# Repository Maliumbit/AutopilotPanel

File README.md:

# AutopilotPanel
Autopilot Controller

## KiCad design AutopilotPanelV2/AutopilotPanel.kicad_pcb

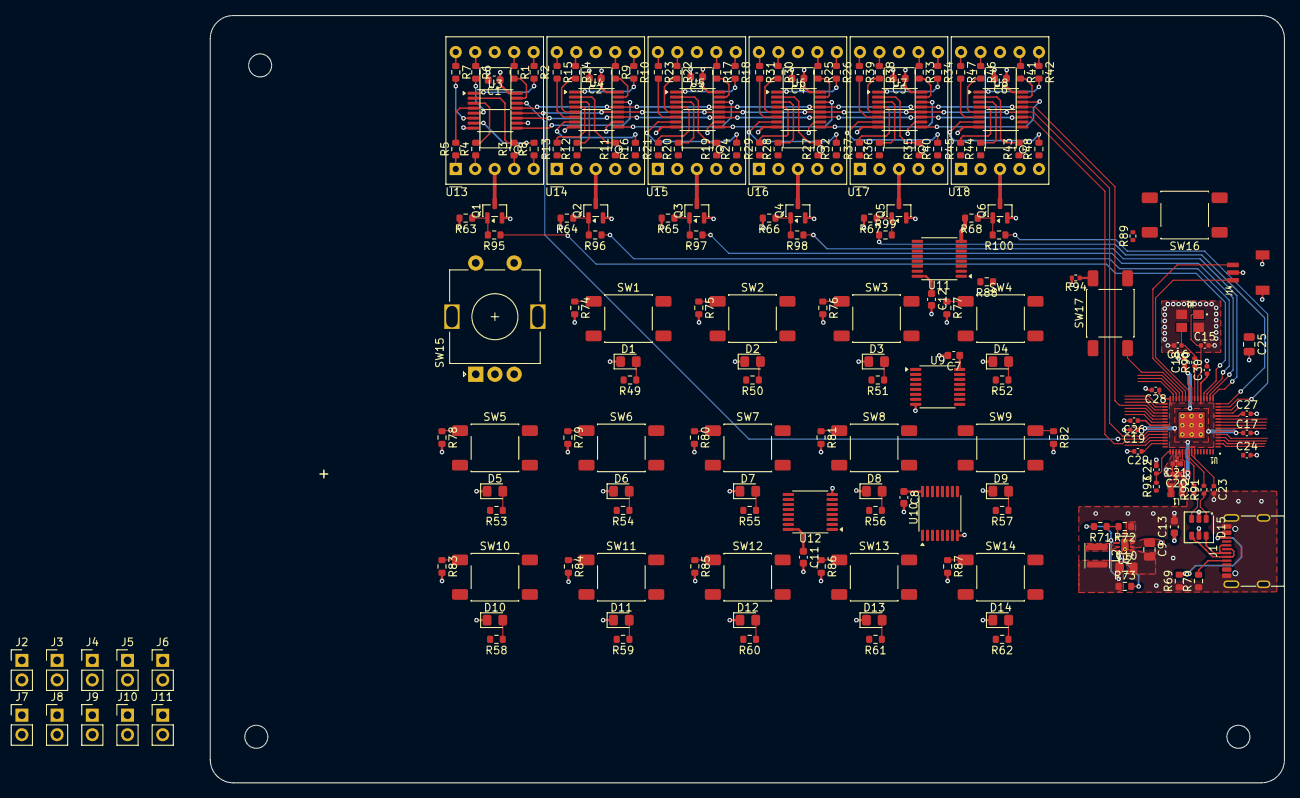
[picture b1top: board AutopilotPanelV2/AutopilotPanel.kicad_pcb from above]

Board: 6 copper layers, 140.0 x 100.0 mm, 200 parts (0 on the bottom side), 203 nets.

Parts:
C1, C2, C3, C4, C5, C6, C7, C8, C11, C12, C13: 100nF; C_0603_1608Metric
C9: 10uF; C_0805_2012Metric
C10: 22uF; C_0805_2012Metric
C15, C16: 15p; C_0402_1005Metric
C17, C18, C19, C23, C24, C26, C27, C28, C29, C30: 100n; C_0402_1005Metric
C20, C21, C22: 4.7u; C_0402_1005Metric
C25: 10u; C_0805_2012Metric
D1, D2, D3, D4, D5, D6, D7, D8, D9, D10, D11, D12, D13, D14: LED_Green_0805; LED_0805_2012Metric_Pad1.15x1.40mm_HandSolder
D15: USBLC6-2SC6; SOT-23-6
J1: USB_C_Receptacle_USB2.0_16P; USB_C_Receptacle_G-Switch_GT-USB-7010ASV
J2, J3, J4, J5, J6, J7, J8, J9, J10, J11: PINHD_1x2_Male; PinHeader_1x02_P2.54mm_Vertical
J14: SM03B-SRSS-TB(LF)(SN); jst_sm03b-srss-tb-lf--sn-
L1: 3.3u; abracon_aota-b201610s3r3-101-t
L2: 2.2uH; L_Changjiang_FNR3015S
Q1, Q2, Q3, Q4, Q5, Q6: NFET-SOT23; SOT-23
R1, R2, R3, R4, R5, R6, R7, R8, R9, R10, R11, R12, R13, R14, R15, R16, R17, R18, R19, R20, R21, R22, R23, R24, R25, R26, R27, R28, R29, R30, R31, R32, R33, R34, R35, R36, R37, R38, R39, R40, R41, R42, R43, R44, R45, R46, R47, R48, R49, R50, R51, R52, R53, R54, R55, R56, R57, R58, R59, R60, R61, R62: 330; R_0603_1608Metric
R63, R64, R65, R66, R67, R68, R74, R75, R76, R77, R78, R79, R80, R81, R82, R83, R84, R85, R86, R87, R88: 10k; R_0603_1608Metric
R69, R70: 5.1k; R_0603_1608Metric
R71: 562k; R_0603_1608Metric
R72: 180k; R_0603_1608Metric
R73: 100k; R_0603_1608Metric
R89, R90, R94: 1k; R_0402_1005Metric
R91, R92: 27; R_0402_1005Metric
R93: 33; R_0402_1005Metric
R95, R96, R97, R98, R99, R100: 100; R_0603_1608Metric
SW1, SW2, SW3, SW4, SW5, SW6, SW7, SW8, SW9, SW10, SW11, SW12, SW13, SW14, SW16, SW17: SW_SPST_Tactile_6x6; SW_Push_1P1T_NO_E-Switch_TL3301NxxxxxG
SW15: RotaryEncoder_Switch_EC11E; RotaryEncoder_Alps_EC11E-Switch_Vertical_H20mm
U1: RP2354A; rpi_rp2350a_vias
U2: TPS62160DSG; Texas_DSG0008A_WSON-8-1EP_2x2mm_P0.5mm_EP0.9x1.6mm_ThermalV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
U3, U4, U5, U6, U7, U8, U9, U10: 74HC595; TSSOP-16_4.4x5mm_P0.65mm
U11, U12: 74HC165; TSSOP-16_4.4x5mm_P0.65mm
U13, U14, U15, U16, U17, U18: 7SegmentFJ5161AH; D1X8K
X1: 12MHz; generic_xtalcc320x250x80-4

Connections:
+1.1V: C17.1, C18.1, C19.1, C20.1, L1.1, U1.6 (DVDD), U1.23 (DVDD), U1.39 (DVDD), U1.50 (VREG_FB)
+3.3V: C1.1, C2.1, C3.1, C4.1, C5.1, C6.1, C7.1, C8.1, C10.1, C11.1, C12.1, C21.1, C23.1, C24.1, C25.1, C26.1, C27.1, C28.1, C29.1, C30.1, J3.1, L2.2, R71.2, R73.1, R88.1, R93.1, SW1.2 (B), SW2.2 (B), SW3.2 (B), SW4.2 (B), SW5.2 (B), SW6.2 (B), SW7.2 (B), SW8.2 (B), SW9.2 (B), SW10.2 (B), SW11.2 (B), SW12.2 (B), SW13.2 (B), SW14.2 (B), U1.1 (IOVDD), U1.11 (IOVDD), U1.20 (IOVDD), U1.30 (IOVDD), U1.38 (IOVDD), U1.44 (ADC_AVDD), U1.45 (IOVDD), U1.49 (VREG_VIN), U1.53 (USB_OTP_VDD), U1.54 (QSPI_IOVDD), U2.6 (VOS), U3.10 (~SRCLR), U3.16 (VCC), U4.10 (~SRCLR), U4.16 (VCC), U5.10 (~SRCLR), U5.16 (VCC), U6.10 (~SRCLR), U6.16 (VCC), U7.10 (~SRCLR), U7.16 (VCC), U8.10 (~SRCLR), U8.16 (VCC), U9.10 (~SRCLR), U9.16 (VCC), U10.10 (~SRCLR), U10.16 (VCC), U11.16 (VCC), U12.16 (VCC)
+5V: C9.1, C13.2, D15.5 (VP), J1.A4 (VBUS), J1.A9 (VBUS), J1.B4 (VBUS), J1.B9 (VBUS), J2.1, U2.2 (VIN), U2.3 (EN)
/GPIO0: SW15.S2, U1.2 (GPIO0)
/GPIO1: SW15.B, U1.3 (GPIO1)
/GPIO2: SW15.A, U1.4 (GPIO2)
/GPIO3: J10.2, U1.5 (GPIO3), U11.2 (CP), U12.2 (CP)
/GPIO4: J8.1, R88.2, U1.7 (GPIO4), U11.1 (~PL), U12.1 (~PL)
/GPIO5: J9.2, U1.8 (GPIO5), U11.9 (Q7)
/GPIO6: J7.2, U1.9 (GPIO6), U9.14 (SER)
/GPIO7: J11.2, U1.10 (GPIO7), U9.11 (SRCLK), U10.11 (SRCLK)
/GPIO8: U1.12 (GPIO8), U9.12 (RCLK), U10.12 (RCLK)
/GPIO9: U1.13 (GPIO9), U9.13 (~OE), U10.13 (~OE)
/GPIO10: R100.1, U1.14 (GPIO10)
/GPIO11: R99.1, U1.15 (GPIO11)
/GPIO12: R98.1, U1.16 (GPIO12)
/GPIO13: R97.1, U1.17 (GPIO13)
/GPIO14: R96.1, U1.18 (GPIO14)
/GPIO15: R95.1, U1.19 (GPIO15)
/GPIO22: U1.34 (GPIO22), U3.13 (~OE), U4.13 (~OE), U5.13 (~OE), U6.13 (~OE), U7.13 (~OE), U8.13 (~OE)
/GPIO26_ADC0: U1.40 (GPIO26_ADC0), U3.12 (RCLK), U4.12 (RCLK), U5.12 (RCLK), U6.12 (RCLK), U7.12 (RCLK), U8.12 (RCLK)
/GPIO27_ADC1: J5.1, U1.41 (GPIO27_ADC1), U3.14 (SER)
/GPIO28_ADC2: J6.1, U1.42 (GPIO28_ADC2), U3.11 (SRCLK), U4.11 (SRCLK), U5.11 (SRCLK), U6.11 (SRCLK), U7.11 (SRCLK), U8.11 (SRCLK)
/QSPI_SS: R89.1, U1.60 (QSPI_~SS)
/RUN: SW17.2 (B), U1.26 (RUN)
/SWCLK: J14.1, U1.24 (SWCLK)
/SWD: J14.3, U1.25 (SWDIO)
/USB_CONN_D+: D15.6 (L1), J1.A6 (D+), J1.B6 (D+)
/USB_CONN_D-: D15.4 (L2), J1.A7 (D-), J1.B7 (D-)
/USB_D+: D15.1 (L1), R91.1
/USB_D-: D15.3 (L2), R92.1
/VREG_AVDD: C22.1, R93.2, U1.46 (VREG_AVDD)
/VREG_LX: L1.2, U1.48 (VREG_LX)
/XIN: C15.1, U1.21 (XIN), X1.1
/XOUT: R90.1, U1.22 (XOUT)
/~USB_BOOT: R89.2, SW16.1 (A)
GND: C1.2, C2.2, C3.2, C4.2, C5.2, C6.2, C7.2, C8.2, C9.2, C10.2, C11.2, C12.2, C13.1, C15.2, C16.2, C17.2, C18.2, C19.2, C20.2, C21.2, C22.2, C23.2, C24.2, C25.2, C26.2, C27.2, C28.2, C29.2, C30.2, D1.1 (K), D2.1 (K), D3.1 (K), D4.1 (K), D5.1 (K), D6.1 (K), D7.1 (K), D8.1 (K), D9.1 (K), D10.1 (K), D11.1 (K), D12.1 (K), D13.1 (K), D14.1 (K), D15.2 (VN), J1.A1 (GND), J1.A12 (GND), J1.B1 (GND), J1.B12 (GND), J1.SH (SHIELD), J2.2, J3.2, J4.1, J5.2, J6.2, J7.1, J8.2, J9.1, J10.1, J11.1, J14.2, J14.4 (SH1), J14.5 (SH2), Q1.2 (S), Q2.2 (S), Q3.2 (S), Q4.2 (S), Q5.2 (S), Q6.2 (S), R63.2, R64.2, R65.2, R66.2, R67.2, R68.2, R69.1, R70.1, R72.1, R74.2, R75.2, R76.2, R77.2, R78.2, R79.2, R80.2, R81.2, R82.2, R83.2, R84.2, R85.2, R86.2, R87.2, R94.2, SW15.C, SW15.MP, SW15.S1, SW16.2 (B), U1.47 (VREG_PGND), U1.61 (GND), U2.1 (PGND), U2.4 (AGND), U2.9 (PAD), U3.8 (GND), U4.8 (GND), U5.8 (GND), U6.8 (GND), U7.8 (GND), U8.8 (GND), U9.8 (GND), U10.8 (GND), U11.8 (GND), U11.15 (~CE), U12.5 (D6), U12.6 (D7), U12.8 (GND), U12.10 (DS), U12.15 (~CE), X1.2, X1.4
unnamed: C16.1, R90.2, X1.3
unnamed: D1.2 (A), R49.1
unnamed: D2.2 (A), R50.1
unnamed: D3.2 (A), R51.1
unnamed: D4.2 (A), R52.1
unnamed: D5.2 (A), R53.1
unnamed: D6.2 (A), R54.1
unnamed: D7.2 (A), R55.1
unnamed: D8.2 (A), R56.1
unnamed: D9.2 (A), R57.1
unnamed: D10.2 (A), R58.1
unnamed: D11.2 (A), R59.1
unnamed: D12.2 (A), R60.1
unnamed: D13.2 (A), R61.1
unnamed: D14.2 (A), R62.1
unnamed: J1.A5 (CC1), R70.2
unnamed: J1.B5 (CC2), R69.2
unnamed: Q1.3 (D), U13.3 (CC), U13.8 (CC)
unnamed: J4.2, Q1.1 (G), R63.1, R95.2
unnamed: Q2.3 (D), U14.3 (CC), U14.8 (CC)
unnamed: Q2.1 (G), R64.1, R96.2
unnamed: Q3.3 (D), U15.3 (CC), U15.8 (CC)
unnamed: Q3.1 (G), R65.1, R97.2
unnamed: Q4.3 (D), U16.3 (CC), U16.8 (CC)
unnamed: Q4.1 (G), R66.1, R98.2
unnamed: Q5.3 (D), U17.3 (CC), U17.8 (CC)
unnamed: Q5.1 (G), R67.1, R99.2
unnamed: Q6.3 (D), U18.3 (CC), U18.8 (CC)
unnamed: Q6.1 (G), R68.1, R100.2
unnamed: R74.1, SW1.1 (A), U11.11 (D0)
unnamed: R75.1, SW2.1 (A), U11.12 (D1)
unnamed: R76.1, SW3.1 (A), U11.13 (D2)
unnamed: R77.1, SW4.1 (A), U11.14 (D3)
unnamed: R78.1, SW5.1 (A), U11.3 (D4)
unnamed: R79.1, SW6.1 (A), U11.4 (D5)
unnamed: R80.1, SW7.1 (A), U11.5 (D6)
unnamed: R81.1, SW8.1 (A), U11.6 (D7)
unnamed: R82.1, SW9.1 (A), U12.11 (D0)
unnamed: R83.1, SW10.1 (A), U12.12 (D1)
unnamed: R84.1, SW11.1 (A), U12.13 (D2)
unnamed: R85.1, SW12.1 (A), U12.14 (D3)
unnamed: R86.1, SW13.1 (A), U12.3 (D4)
unnamed: R87.1, SW14.1 (A), U12.4 (D5)
unnamed: R94.1, SW17.1 (A)
unnamed: R92.2, U1.51 (USB_DM)
unnamed: R91.2, U1.52 (USB_DP)
unnamed: R71.1, R72.2, U2.5 (FB)
unnamed: R73.2, U2.8 (PG)
unnamed: L2.1, U2.7 (SW)
unnamed: R1.2, U3.15 (QA)
unnamed: R2.2, U3.1 (QB)
unnamed: R3.2, U3.2 (QC)
unnamed: R4.2, U3.3 (QD)
unnamed: R5.2, U3.4 (QE)
unnamed: R6.2, U3.5 (QF)
unnamed: R7.2, U3.6 (QG)
unnamed: U3.9 (QH'), U4.14 (SER)
unnamed: R8.2, U3.7 (QH)
unnamed: R9.2, U4.15 (QA)
unnamed: R10.2, U4.1 (QB)
unnamed: R11.2, U4.2 (QC)
unnamed: R12.2, U4.3 (QD)
unnamed: R13.2, U4.4 (QE)
unnamed: R14.2, U4.5 (QF)
unnamed: R15.2, U4.6 (QG)
unnamed: U4.9 (QH'), U5.14 (SER)
unnamed: R16.2, U4.7 (QH)
unnamed: R17.2, U5.15 (QA)
unnamed: R18.2, U5.1 (QB)
unnamed: R19.2, U5.2 (QC)
unnamed: R20.2, U5.3 (QD)
unnamed: R21.2, U5.4 (QE)
unnamed: R22.2, U5.5 (QF)
unnamed: R23.2, U5.6 (QG)
unnamed: U5.9 (QH'), U6.14 (SER)
unnamed: R24.2, U5.7 (QH)
unnamed: R25.2, U6.15 (QA)
unnamed: R26.2, U6.1 (QB)
unnamed: R27.2, U6.2 (QC)
unnamed: R28.2, U6.3 (QD)
unnamed: R29.2, U6.4 (QE)
unnamed: R30.2, U6.5 (QF)
unnamed: R31.2, U6.6 (QG)
unnamed: U6.9 (QH'), U7.14 (SER)
unnamed: R32.2, U6.7 (QH)
unnamed: R33.2, U7.15 (QA)
unnamed: R34.2, U7.1 (QB)
unnamed: R35.2, U7.2 (QC)
unnamed: R36.2, U7.3 (QD)
unnamed: R37.2, U7.4 (QE)
unnamed: R38.2, U7.5 (QF)
unnamed: R39.2, U7.6 (QG)
unnamed: U7.9 (QH'), U8.14 (SER)
unnamed: R40.2, U7.7 (QH)
unnamed: R41.2, U8.15 (QA)
unnamed: R42.2, U8.1 (QB)
unnamed: R43.2, U8.2 (QC)
unnamed: R44.2, U8.3 (QD)
unnamed: R45.2, U8.4 (QE)
unnamed: R46.2, U8.5 (QF)
unnamed: R47.2, U8.6 (QG)
unnamed: R48.2, U8.7 (QH)
unnamed: R49.2, U9.15 (QA)
unnamed: R50.2, U9.1 (QB)
unnamed: R51.2, U9.2 (QC)
unnamed: R52.2, U9.3 (QD)
unnamed: R53.2, U9.4 (QE)
unnamed: R54.2, U9.5 (QF)
unnamed: R55.2, U9.6 (QG)
unnamed: R56.2, U9.7 (QH)
unnamed: R57.2, U10.15 (QA)
unnamed: R58.2, U10.1 (QB)
unnamed: R59.2, U10.2 (QC)
unnamed: R60.2, U10.3 (QD)
unnamed: R61.2, U10.4 (QE)
unnamed: R62.2, U10.5 (QF)
unnamed: U9.9 (QH'), U10.14 (SER)
unnamed: U11.10 (DS), U12.9 (Q7)
unnamed: R1.1, U13.7 (A)
unnamed: R2.1, U13.6 (B)
unnamed: R3.1, U13.4 (C)
unnamed: R4.1, U13.2 (D)
unnamed: R8.1, U13.5 (DP)
unnamed: R5.1, U13.1 (E)
unnamed: R6.1, U13.9 (F)
unnamed: R7.1, U13.10 (G)
unnamed: R9.1, U14.7 (A)
unnamed: R10.1, U14.6 (B)
unnamed: R11.1, U14.4 (C)
unnamed: R12.1, U14.2 (D)
unnamed: R16.1, U14.5 (DP)
unnamed: R13.1, U14.1 (E)
unnamed: R14.1, U14.9 (F)
unnamed: R15.1, U14.10 (G)
unnamed: R17.1, U15.7 (A)
unnamed: R18.1, U15.6 (B)
unnamed: R19.1, U15.4 (C)
unnamed: R20.1, U15.2 (D)
unnamed: R24.1, U15.5 (DP)
unnamed: R21.1, U15.1 (E)
unnamed: R22.1, U15.9 (F)
unnamed: R23.1, U15.10 (G)
unnamed: R25.1, U16.7 (A)
unnamed: R26.1, U16.6 (B)
unnamed: R27.1, U16.4 (C)
unnamed: R28.1, U16.2 (D)
unnamed: R32.1, U16.5 (DP)
unnamed: R29.1, U16.1 (E)
unnamed: R30.1, U16.9 (F)
unnamed: R31.1, U16.10 (G)
unnamed: R33.1, U17.7 (A)
unnamed: R34.1, U17.6 (B)
unnamed: R35.1, U17.4 (C)
unnamed: R36.1, U17.2 (D)
unnamed: R40.1, U17.5 (DP)
unnamed: R37.1, U17.1 (E)
unnamed: R38.1, U17.9 (F)
unnamed: R39.1, U17.10 (G)
unnamed: R41.1, U18.7 (A)
unnamed: R42.1, U18.6 (B)
unnamed: R43.1, U18.4 (C)
unnamed: R44.1, U18.2 (D)
unnamed: R48.1, U18.5 (DP)
unnamed: R45.1, U18.1 (E)
unnamed: R46.1, U18.9 (F)
unnamed: R47.1, U18.10 (G)

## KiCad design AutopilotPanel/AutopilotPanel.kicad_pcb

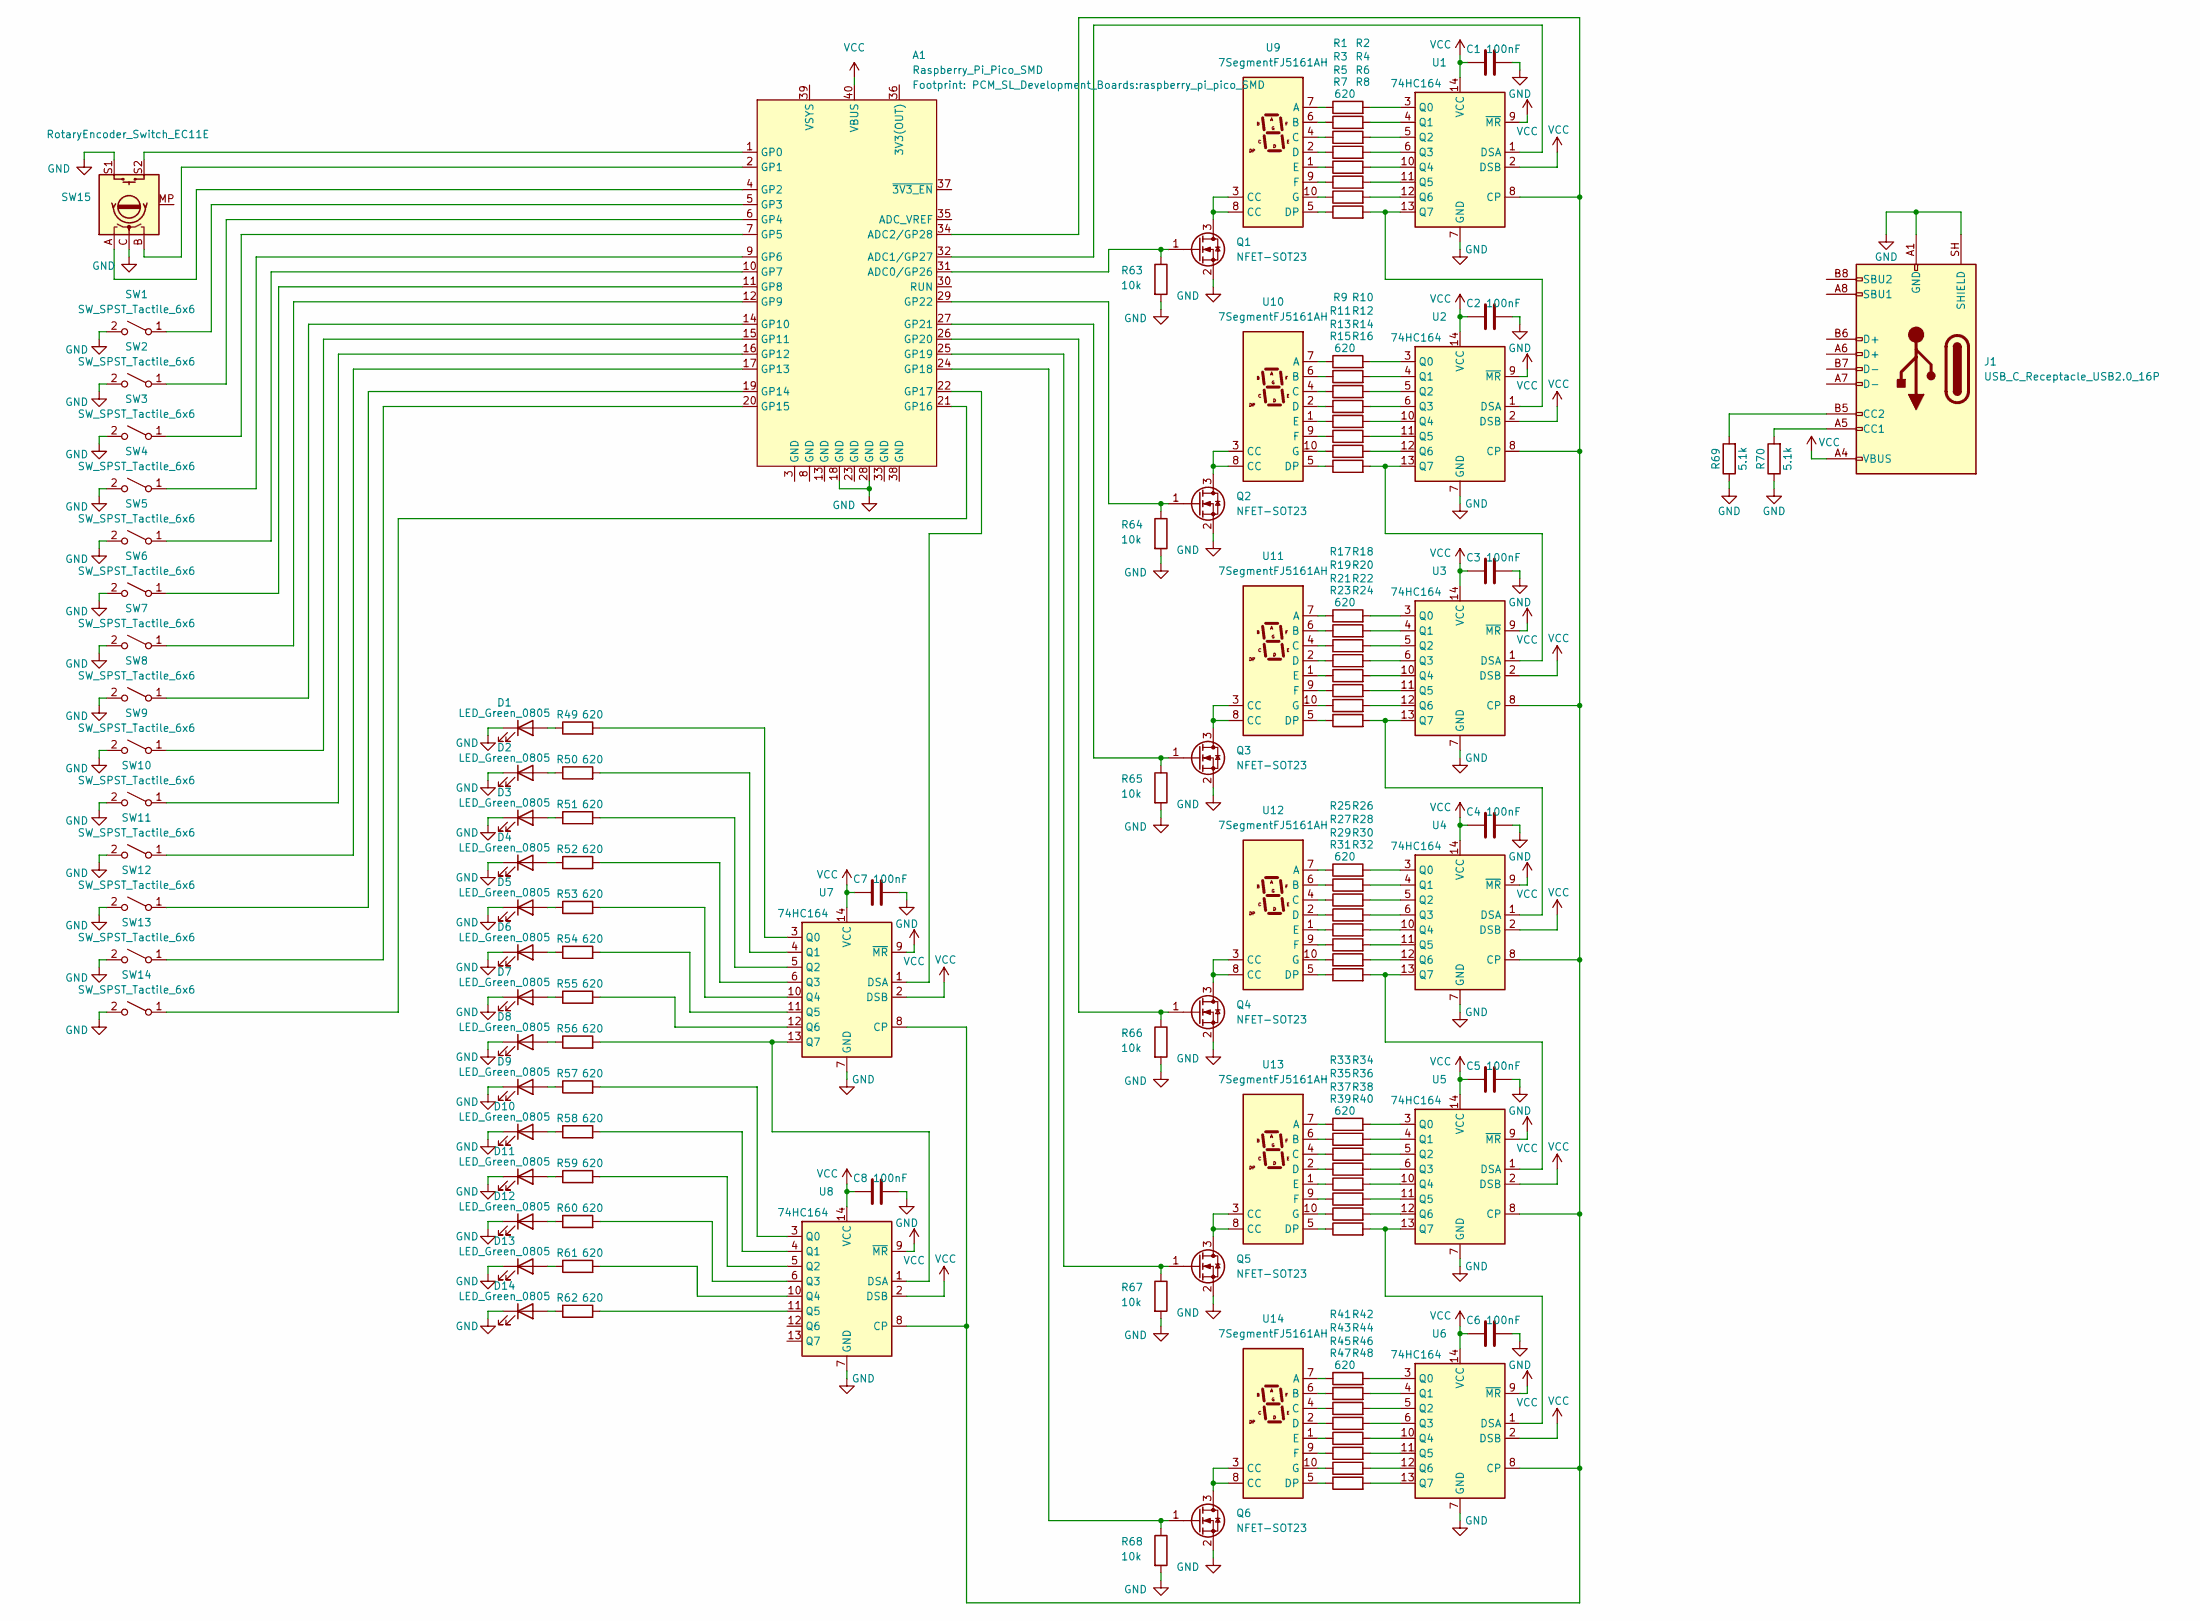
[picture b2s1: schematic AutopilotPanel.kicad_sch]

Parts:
A1: Raspberry_Pi_Pico_SMD; raspberry_pi_pico_SMD
C1, C2, C3, C4, C5, C6, C7, C8: 100nF; C_0805_2012Metric_Pad1.18x1.45mm_HandSolder
D1, D2, D3, D4, D5, D6, D7, D8, D9, D10, D11, D12, D13, D14: LED_Green_0805; LED_0805_2012Metric_Pad1.15x1.40mm_HandSolder
J1: USB_C_Receptacle_USB2.0_16P; USB_C_Receptacle_G-Switch_GT-USB-7010ASV
Q1, Q2, Q3, Q4, Q5, Q6: NFET-SOT23; SOT-23
R1, R2, R3, R4, R5, R6, R7, R8, R9, R10, R11, R12, R13, R14, R15, R16, R17, R18, R19, R20, R21, R22, R23, R24, R25, R26, R27, R28, R29, R30, R31, R32, R33, R34, R35, R36, R37, R38, R39, R40, R41, R42, R43, R44, R45, R46, R47, R48, R49, R50, R51, R52, R53, R54, R55, R56, R57, R58, R59, R60, R61, R62: 620; R_0805_2012Metric_Pad1.20x1.40mm_HandSolder
R63, R64, R65, R66, R67, R68: 10k; R_0805_2012Metric_Pad1.20x1.40mm_HandSolder
R69, R70: 5.1k; R_0805_2012Metric_Pad1.20x1.40mm_HandSolder
SW1, SW2, SW3, SW4, SW5, SW6, SW7, SW8, SW9, SW10, SW11, SW12, SW13, SW14: SW_SPST_Tactile_6x6; SW_Push_1P1T_NO_E-Switch_TL3301NxxxxxG
SW15: RotaryEncoder_Switch_EC11E; RotaryEncoder_Alps_EC11E-Switch_Vertical_H20mm
U1, U2, U3, U4, U5, U6, U7, U8: 74HC164; SOIC-14_3.9x8.7mm_P1.27mm
U9, U10, U11, U12, U13, U14: 7SegmentFJ5161AH; D1X8K

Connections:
GND: A1.18 (GND), A1.28 (GND), C1.2, C2.2, C3.2, C4.2, C5.2, C6.2, C7.2, C8.2, D1.1 (K), D2.1 (K), D3.1 (K), D4.1 (K), D5.1 (K), D6.1 (K), D7.1 (K), D8.1 (K), D9.1 (K), D10.1 (K), D11.1 (K), D12.1 (K), D13.1 (K), D14.1 (K), J1.A1 (GND), J1.A12 (GND), J1.B1 (GND), J1.B12 (GND), J1.SH (SHIELD), Q1.2 (S), Q2.2 (S), Q3.2 (S), Q4.2 (S), Q5.2 (S), Q6.2 (S), R63.2, R64.2, R65.2, R66.2, R67.2, R68.2, R69.1, R70.1, SW1.2 (B), SW2.2 (B), SW3.2 (B), SW4.2 (B), SW5.2 (B), SW6.2 (B), SW7.2 (B), SW8.2 (B), SW9.2 (B), SW10.2 (B), SW11.2 (B), SW12.2 (B), SW13.2 (B), SW14.2 (B), SW15.C, SW15.S1, U1.7 (GND), U2.7 (GND), U3.7 (GND), U4.7 (GND), U5.7 (GND), U6.7 (GND), U7.7 (GND), U8.7 (GND)
unnamed: A1.31 (ADC0/GP26), Q1.1 (G), R63.1
unnamed: A1.32 (ADC1/GP27), U1.1 (DSA)
unnamed: A1.34 (ADC2/GP28), U1.8 (CP), U2.8 (CP), U3.8 (CP), U4.8 (CP), U5.8 (CP), U6.8 (CP), U7.8 (CP), U8.8 (CP)
unnamed: A1.1 (GP0), SW15.S2
unnamed: A1.2 (GP1), SW15.B
unnamed: A1.4 (GP2), SW15.A
unnamed: A1.5 (GP3), SW1.1 (A)
unnamed: A1.6 (GP4), SW2.1 (A)
unnamed: A1.7 (GP5), SW3.1 (A)
unnamed: A1.9 (GP6), SW4.1 (A)
unnamed: A1.10 (GP7), SW5.1 (A)
unnamed: A1.11 (GP8), SW6.1 (A)
unnamed: A1.12 (GP9), SW7.1 (A)
unnamed: A1.14 (GP10), SW8.1 (A)
unnamed: A1.15 (GP11), SW9.1 (A)
unnamed: A1.16 (GP12), SW10.1 (A)
unnamed: A1.17 (GP13), SW11.1 (A)
unnamed: A1.19 (GP14), SW12.1 (A)
unnamed: A1.20 (GP15), SW13.1 (A)
unnamed: A1.21 (GP16), SW14.1 (A)
unnamed: A1.22 (GP17), U7.1 (DSA)
unnamed: A1.24 (GP18), Q6.1 (G), R68.1
unnamed: A1.25 (GP19), Q5.1 (G), R67.1
unnamed: A1.26 (GP20), Q4.1 (G), R66.1
unnamed: A1.27 (GP21), Q3.1 (G), R65.1
unnamed: A1.29 (GP22), Q2.1 (G), R64.1
unnamed: D1.2 (A), R49.1
unnamed: D2.2 (A), R50.1
unnamed: D3.2 (A), R51.1
unnamed: D4.2 (A), R52.1
unnamed: D5.2 (A), R53.1
unnamed: D6.2 (A), R54.1
unnamed: D7.2 (A), R55.1
unnamed: D8.2 (A), R56.1
unnamed: D9.2 (A), R57.1
unnamed: D10.2 (A), R58.1
unnamed: D11.2 (A), R59.1
unnamed: D12.2 (A), R60.1
unnamed: D13.2 (A), R61.1
unnamed: D14.2 (A), R62.1
unnamed: J1.A5 (CC1), R70.2
unnamed: J1.B5 (CC2), R69.2
unnamed: Q1.3 (D), U9.3 (CC), U9.8 (CC)
unnamed: Q2.3 (D), U10.3 (CC), U10.8 (CC)
unnamed: Q3.3 (D), U11.3 (CC), U11.8 (CC)
unnamed: Q4.3 (D), U12.3 (CC), U12.8 (CC)
unnamed: Q5.3 (D), U13.3 (CC), U13.8 (CC)
unnamed: Q6.3 (D), U14.3 (CC), U14.8 (CC)
unnamed: R1.2, U1.3 (Q0)
unnamed: R2.2, U1.4 (Q1)
unnamed: R3.2, U1.5 (Q2)
unnamed: R4.2, U1.6 (Q3)
unnamed: R5.2, U1.10 (Q4)
unnamed: R6.2, U1.11 (Q5)
unnamed: R7.2, U1.12 (Q6)
unnamed: R8.2, U1.13 (Q7), U2.1 (DSA)
unnamed: R9.2, U2.3 (Q0)
unnamed: R10.2, U2.4 (Q1)
unnamed: R11.2, U2.5 (Q2)
unnamed: R12.2, U2.6 (Q3)
unnamed: R13.2, U2.10 (Q4)
unnamed: R14.2, U2.11 (Q5)
unnamed: R15.2, U2.12 (Q6)
unnamed: R16.2, U2.13 (Q7), U3.1 (DSA)
unnamed: R17.2, U3.3 (Q0)
unnamed: R18.2, U3.4 (Q1)
unnamed: R19.2, U3.5 (Q2)
unnamed: R20.2, U3.6 (Q3)
unnamed: R21.2, U3.10 (Q4)
unnamed: R22.2, U3.11 (Q5)
unnamed: R23.2, U3.12 (Q6)
unnamed: R24.2, U3.13 (Q7), U4.1 (DSA)
unnamed: R25.2, U4.3 (Q0)
unnamed: R26.2, U4.4 (Q1)
unnamed: R27.2, U4.5 (Q2)
unnamed: R28.2, U4.6 (Q3)
unnamed: R29.2, U4.10 (Q4)
unnamed: R30.2, U4.11 (Q5)
unnamed: R31.2, U4.12 (Q6)
unnamed: R32.2, U4.13 (Q7), U5.1 (DSA)
unnamed: R33.2, U5.3 (Q0)
unnamed: R34.2, U5.4 (Q1)
unnamed: R35.2, U5.5 (Q2)
unnamed: R36.2, U5.6 (Q3)
unnamed: R37.2, U5.10 (Q4)
unnamed: R38.2, U5.11 (Q5)
unnamed: R39.2, U5.12 (Q6)
unnamed: R40.2, U5.13 (Q7), U6.1 (DSA)
unnamed: R41.2, U6.3 (Q0)
unnamed: R42.2, U6.4 (Q1)
unnamed: R43.2, U6.5 (Q2)
unnamed: R44.2, U6.6 (Q3)
unnamed: R45.2, U6.10 (Q4)
unnamed: R46.2, U6.11 (Q5)
unnamed: R47.2, U6.12 (Q6)
unnamed: R48.2, U6.13 (Q7)
unnamed: R49.2, U7.3 (Q0)
unnamed: R50.2, U7.4 (Q1)
unnamed: R51.2, U7.5 (Q2)
unnamed: R52.2, U7.6 (Q3)
unnamed: R53.2, U7.10 (Q4)
unnamed: R54.2, U7.11 (Q5)
unnamed: R55.2, U7.12 (Q6)
unnamed: R56.2, U7.13 (Q7), U8.1 (DSA)
unnamed: R57.2, U8.3 (Q0)
unnamed: R58.2, U8.4 (Q1)
unnamed: R59.2, U8.5 (Q2)
unnamed: R60.2, U8.6 (Q3)
unnamed: R61.2, U8.10 (Q4)
unnamed: R62.2, U8.11 (Q5)
unnamed: R1.1, U9.7 (A)
unnamed: R2.1, U9.6 (B)
unnamed: R3.1, U9.4 (C)
unnamed: R4.1, U9.2 (D)
unnamed: R8.1, U9.5 (DP)
unnamed: R5.1, U9.1 (E)
unnamed: R6.1, U9.9 (F)
unnamed: R7.1, U9.10 (G)
unnamed: R9.1, U10.7 (A)
unnamed: R10.1, U10.6 (B)
unnamed: R11.1, U10.4 (C)
unnamed: R12.1, U10.2 (D)
unnamed: R16.1, U10.5 (DP)
unnamed: R13.1, U10.1 (E)
unnamed: R14.1, U10.9 (F)
unnamed: R15.1, U10.10 (G)
unnamed: R17.1, U11.7 (A)
unnamed: R18.1, U11.6 (B)
unnamed: R19.1, U11.4 (C)
unnamed: R20.1, U11.2 (D)
unnamed: R24.1, U11.5 (DP)
unnamed: R21.1, U11.1 (E)
unnamed: R22.1, U11.9 (F)
unnamed: R23.1, U11.10 (G)
unnamed: R25.1, U12.7 (A)
unnamed: R26.1, U12.6 (B)
unnamed: R27.1, U12.4 (C)
unnamed: R28.1, U12.2 (D)
unnamed: R32.1, U12.5 (DP)
unnamed: R29.1, U12.1 (E)
unnamed: R30.1, U12.9 (F)
unnamed: R31.1, U12.10 (G)
unnamed: R33.1, U13.7 (A)
unnamed: R34.1, U13.6 (B)
unnamed: R35.1, U13.4 (C)
unnamed: R36.1, U13.2 (D)
unnamed: R40.1, U13.5 (DP)
unnamed: R37.1, U13.1 (E)
unnamed: R38.1, U13.9 (F)
unnamed: R39.1, U13.10 (G)
unnamed: R41.1, U14.7 (A)
unnamed: R42.1, U14.6 (B)
unnamed: R43.1, U14.4 (C)
unnamed: R44.1, U14.2 (D)
unnamed: R48.1, U14.5 (DP)
unnamed: R45.1, U14.1 (E)
unnamed: R46.1, U14.9 (F)
unnamed: R47.1, U14.10 (G)
VCC: A1.40 (VBUS), C1.1, C2.1, C3.1, C4.1, C5.1, C6.1, C7.1, C8.1, J1.A4 (VBUS), J1.A9 (VBUS), J1.B4 (VBUS), J1.B9 (VBUS), U1.2 (DSB), U1.9 (~MR), U1.14 (VCC), U2.2 (DSB), U2.9 (~MR), U2.14 (VCC), U3.2 (DSB), U3.9 (~MR), U3.14 (VCC), U4.2 (DSB), U4.9 (~MR), U4.14 (VCC), U5.2 (DSB), U5.9 (~MR), U5.14 (VCC), U6.2 (DSB), U6.9 (~MR), U6.14 (VCC), U7.2 (DSB), U7.9 (~MR), U7.14 (VCC), U8.2 (DSB), U8.9 (~MR), U8.14 (VCC)

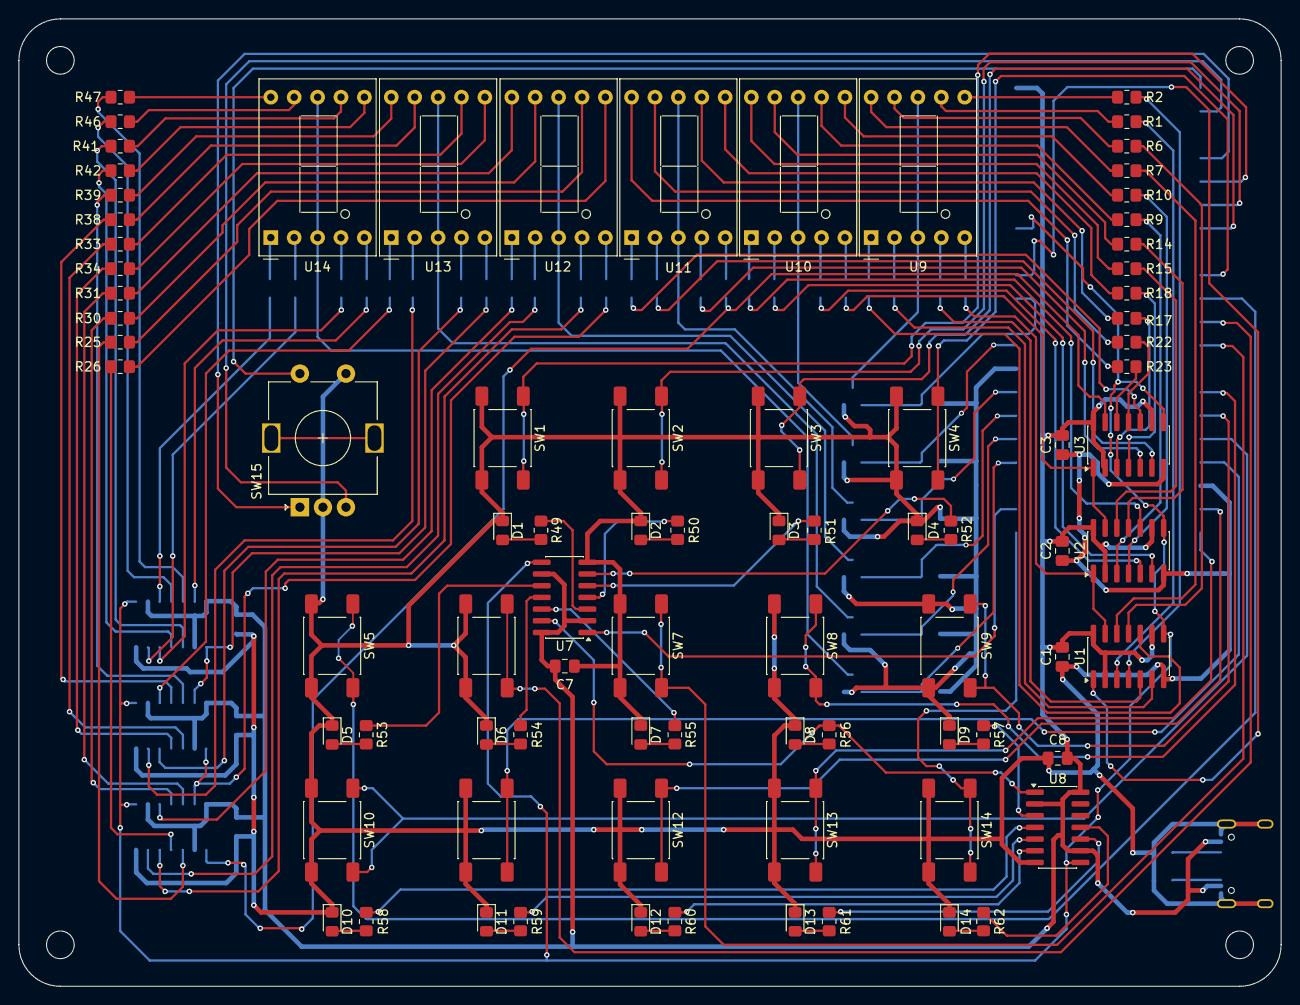
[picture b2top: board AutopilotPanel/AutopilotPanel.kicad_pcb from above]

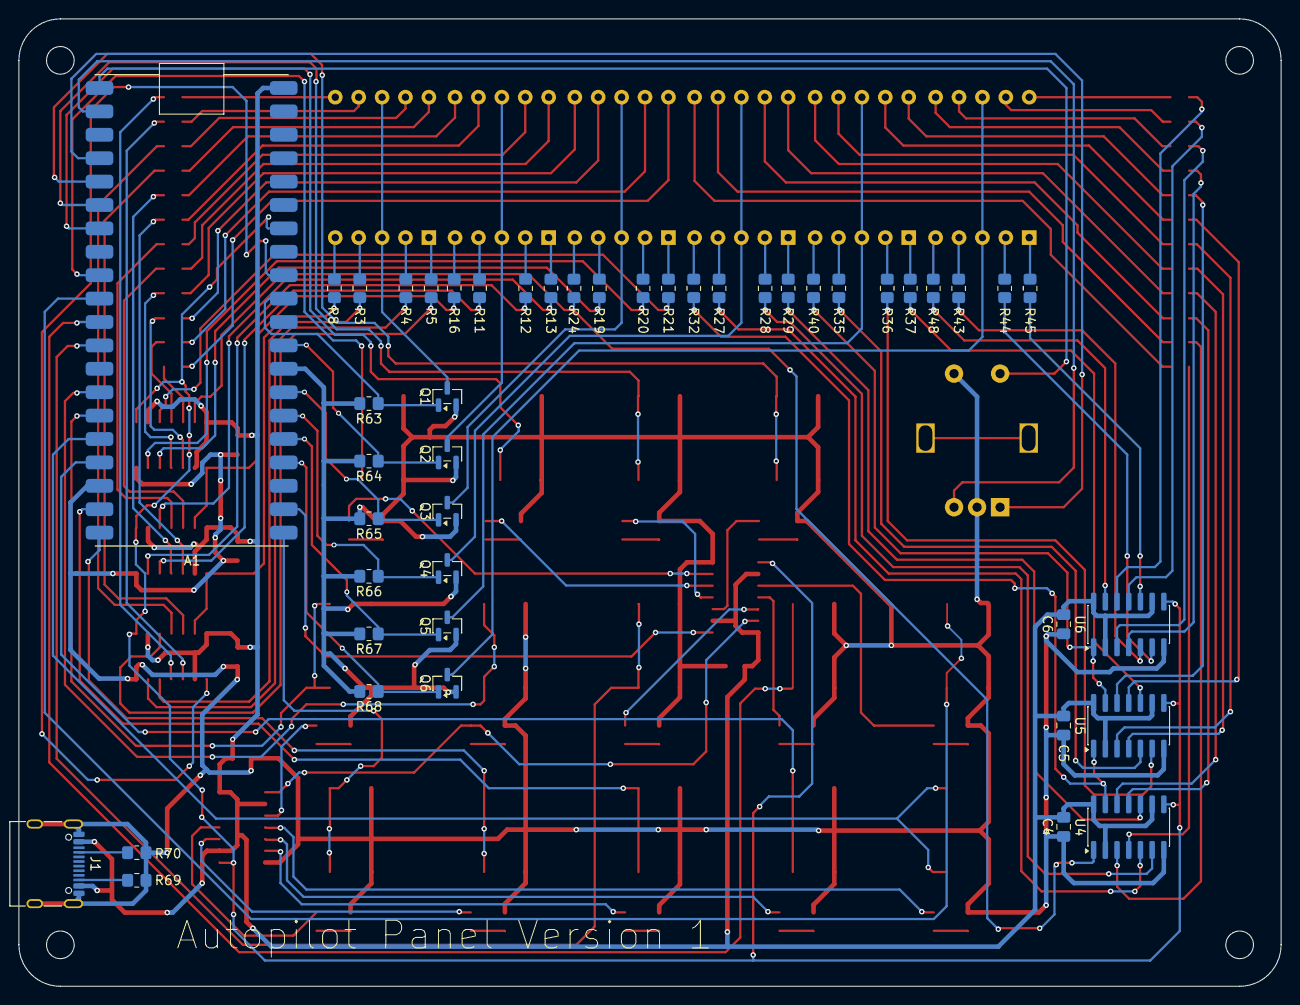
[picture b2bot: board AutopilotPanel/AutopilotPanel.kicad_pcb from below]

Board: 2 copper layers, 137.0 x 105.0 mm, 129 parts (46 on the bottom side), 160 nets.
